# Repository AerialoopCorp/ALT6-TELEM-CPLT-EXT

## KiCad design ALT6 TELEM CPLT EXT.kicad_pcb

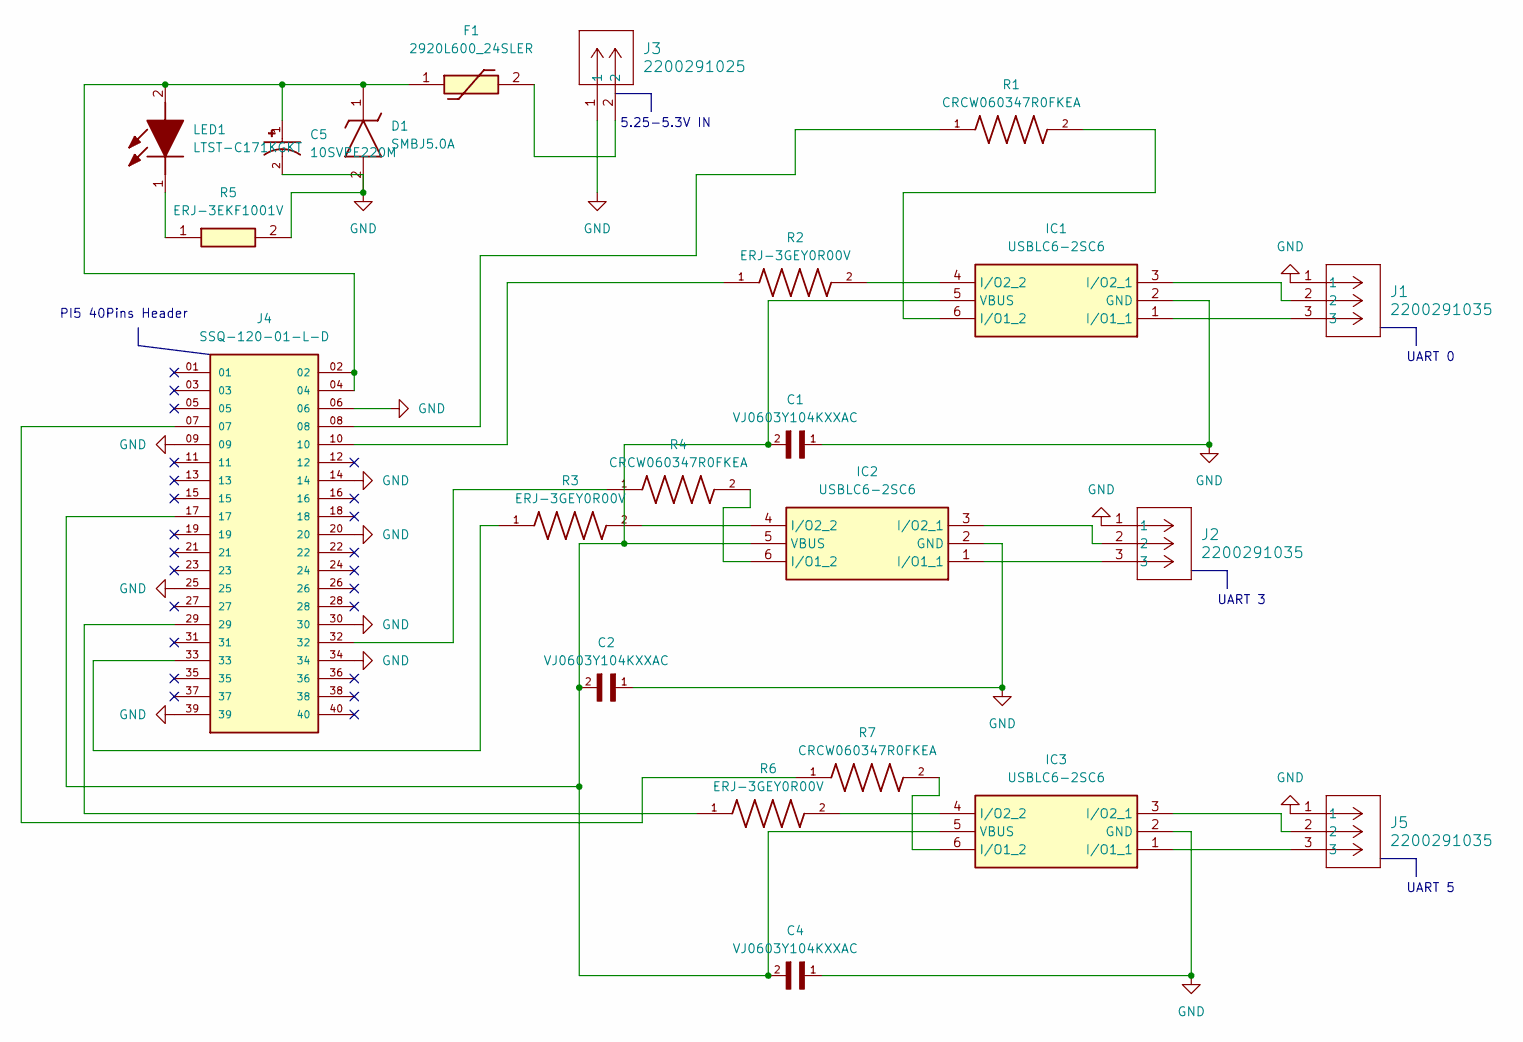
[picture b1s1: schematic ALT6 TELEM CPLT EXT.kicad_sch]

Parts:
C1, C2, C4: VJ0603Y104KXXAC; CAPC1608X97N
C5: 10SVPE220M; CAP_10SVPE220M; PARTREV 28-Jun-19
D1: SMBJ5.0A; DIOM5436X261N; Mouser Part Number 576-SMBJ5.0A
F1: 2920L600_24SLER; 2920L700SLPR; Mouser Part Number 576-2920L600/24SLER
IC1, IC2, IC3: USBLC6-2SC6; SOT95P280X145-6N; Mouser Part Number 511-USBLC6-2SC6
J1, J2, J5: 2200291035; CONN_2200290000-SD_03_MOL
J3: 2200291025; CONN_2200290000-SD_02_MOL
J4: SSQ-120-01-L-D; SAMTEC_SSQ-120-01-L-D; PARTREV R
LED1: LTST-C171KGKT; LEDC2012X90N; Mouser Part Number 859-LTST-C171KGKT
R1, R4, R7: CRCW060347R0FKEA; RESC1508X50N
R2, R3, R6: ERJ-3GEY0R00V; RES_ERJ-3GEY0R00V; PARTREV 3/1/2020
R5: ERJ-3EKF1001V; RESC1608X55N; Mouser Part Number 667-ERJ-3EKF1001V

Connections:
GND: C1.1, C2.1, C4.1, C5.2, D1.2 (A), IC1.2 (GND), IC2.2 (GND), IC3.2 (GND), J1.1, J2.1, J3.1, J4.06, J4.09, J4.14, J4.20, J4.25, J4.30, J4.34, J4.39, J5.1, R5.2
unnamed: C5.1, D1.1 (K), F1.1, J4.02, J4.04, LED1.2 (A)
unnamed: F1.2, J3.2
unnamed: IC1.1 (I/O1_1), J1.3
unnamed: IC1.6 (I/O1_2), R1.2
unnamed: IC1.3 (I/O2_1), J1.2
unnamed: IC1.4 (I/O2_2), R2.2
unnamed: C1.2, C2.2, C4.2, IC1.5 (VBUS), IC2.5 (VBUS), IC3.5 (VBUS), J4.17
unnamed: IC2.1 (I/O1_1), J2.3
unnamed: IC2.6 (I/O1_2), R4.2
unnamed: IC2.3 (I/O2_1), J2.2
unnamed: IC2.4 (I/O2_2), R3.2
unnamed: IC3.1 (I/O1_1), J5.3
unnamed: IC3.6 (I/O1_2), R7.2
unnamed: IC3.3 (I/O2_1), J5.2
unnamed: IC3.4 (I/O2_2), R6.2
unnamed: J4.07, R7.1
unnamed: J4.08, R1.1
unnamed: J4.10, R2.1
unnamed: J4.29, R6.1
unnamed: J4.32, R4.1
unnamed: J4.33, R3.1
unnamed: LED1.1 (K), R5.1

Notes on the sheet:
PI5 40Pins Header
UART 0
5.25-5.3V IN
UART 5
UART 3

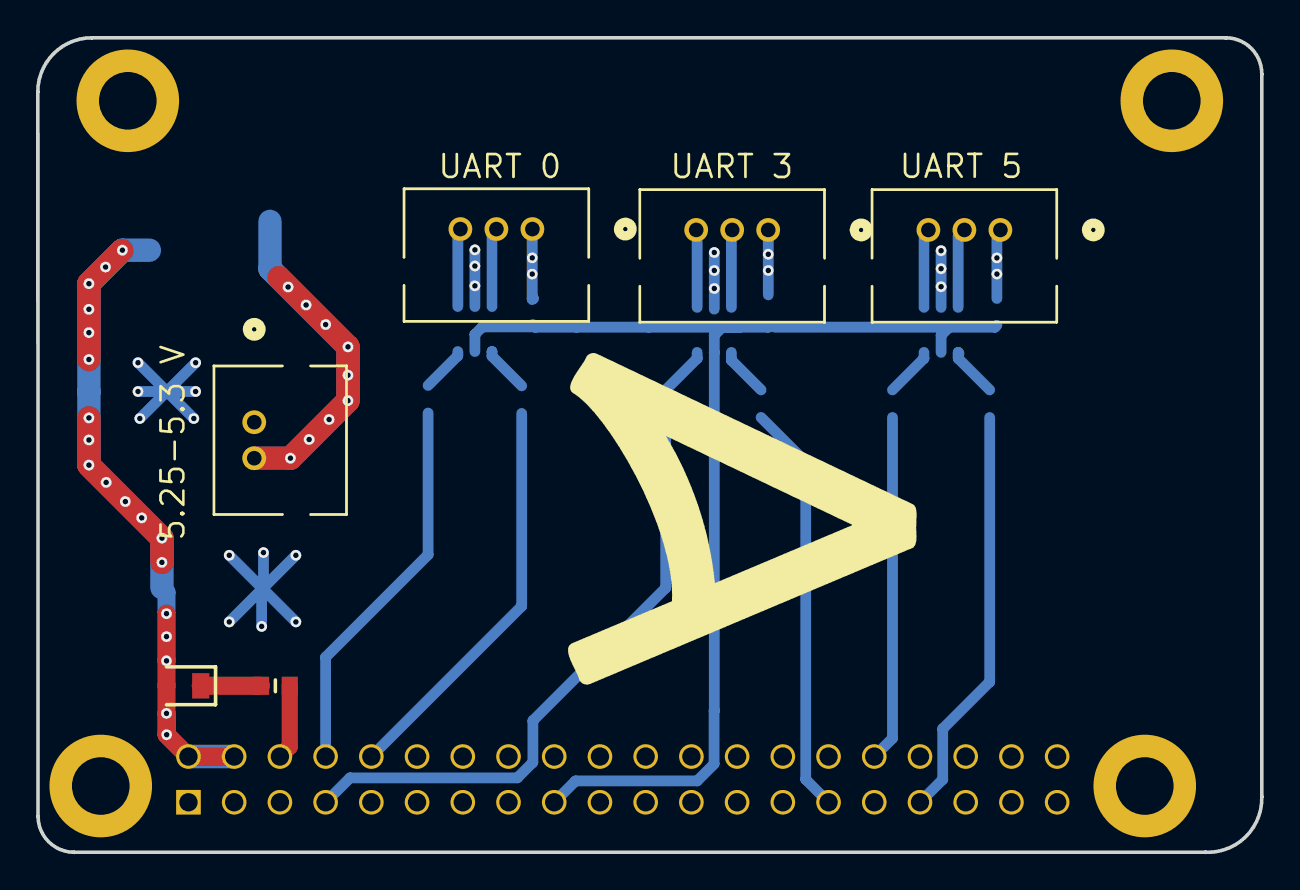
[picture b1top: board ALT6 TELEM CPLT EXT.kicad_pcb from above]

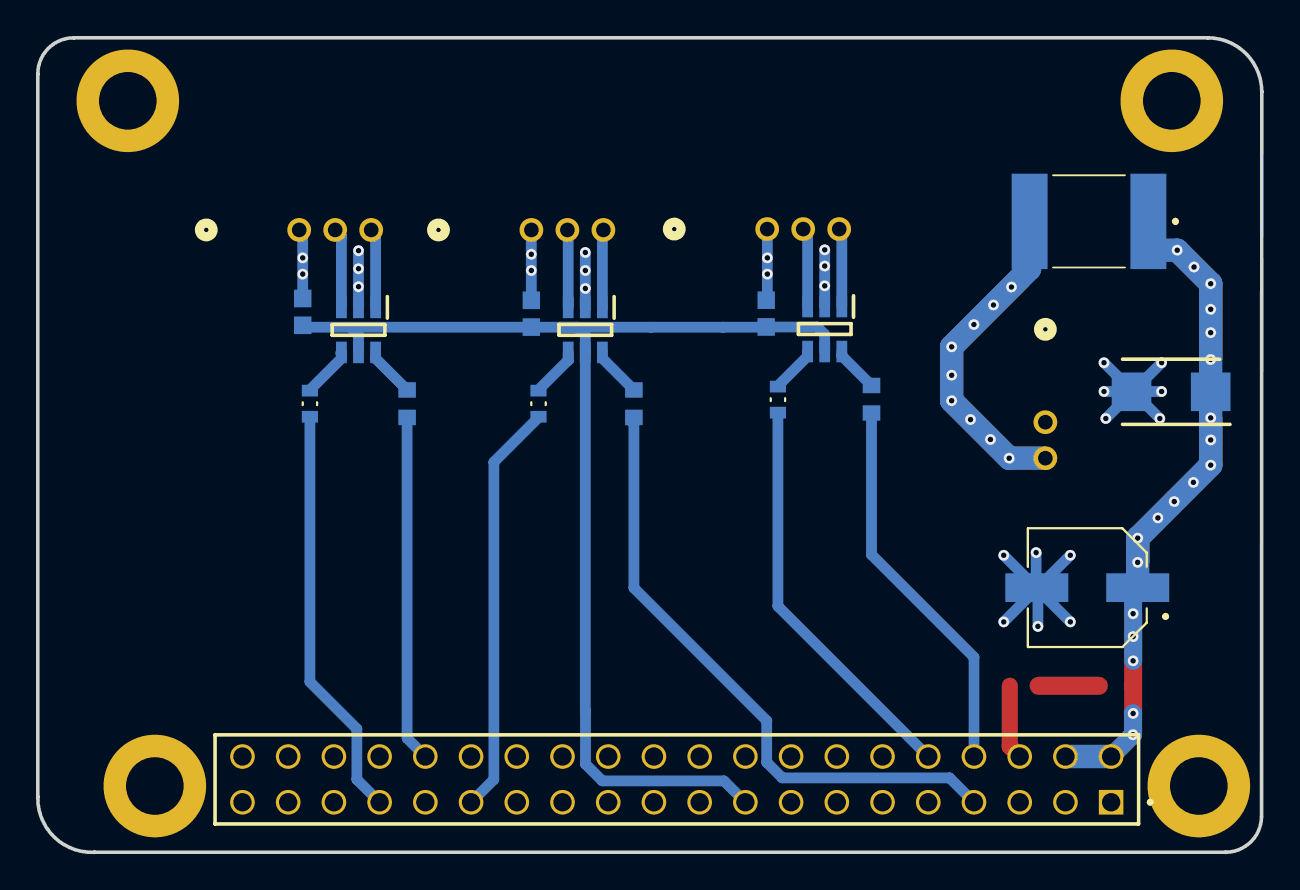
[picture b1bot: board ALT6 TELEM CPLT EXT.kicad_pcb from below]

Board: 4 copper layers, 68.0 x 45.2 mm, 22 parts (16 on the bottom side), 23 nets.

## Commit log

2026-02-25 Connectors change
    Connectors change to vertical, improve trace design, add 0ohm in RX line to test, change the power connector (was very big and innecesary)
2026-03-13 Complete Schematic
    added labels in the schematic
2026-03-13 gitignore
    add exclusions
2026-03-13 Reupload footprints
